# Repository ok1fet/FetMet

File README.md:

<!-- formatovani Markdown nebo html
kdyz neni obrazek 800x600 

<p>Celkové schéma zapojení.</p>
</p> 
-->

# FetMet APRS amatérská LoRa meteostanice

🟥**Nová verze poporuje posílání dat přes protokol MQTT**🟥

Meteostanice je postavena na vývojové desce ESP32 LILYGO T3 v1.6.1, která obsahuje integrovaný LoRa modul (433 MHz) a OLED displej. Díky tomu je celá konstrukce sondy výrazně zjednodušená.

Pro měření směru a rychlosti větru, srážek, atmosférického tlaku, teploty a vlhkosti stačí pouze tři elektronické součástky:
2× kondenzátor, 1× odpor a senzorový modul BME280.

Rychlost větru je měřena každých 20 sekund během intervalu 5 sekund.
Směr větru se vypočítává pomocí Yamartinova algoritmu, který vektorově zpracuje data a provádí korekci směrové odchylky.

Po 24 dvacetisekundových cyklech (tedy každých 10 minut) se provede měření tlaku, teploty a vlhkosti. Výsledná data jsou odesílána prostřednictvím sítě LoRa APRS.

Historická data lze sledovat online na:[www.aprs.fi](https://www.aprs.fi).

🌧️ Měření srážek
Srážky se detekují nepřetržitě s přesností 0,3 mm na impuls data se ukládají průběžně. Každých 10 minut (6 cyklus) se provede součet **6 a 144 polohového kruhového bufferu**, čímž získáme přehled za poslední hodinua den.

🔩 Použité senzory
Senzory pro vítr a srážky jsou převzaty z běžně dostupných meteostanic WH1080 / WH1090, které lze snadno zakoupit jako náhradní díly za přijatelnou cenu.

🧠 Software
Celý kód je bohatě okomentovaný a všechny výpočty jsou průběžně zobrazovány na sériové konzoli během běhu softwaru.

**Celkové schéma zapojení.**

Pohled na prototyp meteosondy MetFet 🙂.

**Doporučení pro solární provoz:**  
Vypni OLED úplně (jumper na GPIO4 propojen na GND)

Montáž sondy do vodotěsné krabičky.

Pohled na stranu plošného spoje.

## Spotřeba – naměřená na stole

| Režim                     | OLED zapnutý | OLED vypnutý (GPIO4 = LOW) |
|---------------------------|--------------|----------------------------|
| Deep-sleep                | 5,0 mA       | **1,9 mA**                 |
| Měření větru (3 s)        | 22 mA        | **19,5 mA**                |
| LoRa vysílání             | 89 mA        | **80 mA**                  |

Ukázka montáže za využití 3D tištěných dílů.

Detail konzole se senzory větru.

Testování J antény.

Upravené Moxon antény.

Orientační kalibrace srážkoměru za pomocí zahradního kolečka. 😅

## Co a jak přesně měří

| Velicina            | Rozlišení / přesnost               | Interval měření |
|---------------------|------------------------------------|-----------------|
| Rychlost větru      | 0,1 m/s (1 impuls ≈ 2,4 km/h)      | každých 20 s    |
| Směr větru          | 8 směrů + Yamartinův algoritmus    | každých 20 s    |
| Srážky              | 0,3 mm na impuls                   | nepřetržitě     |
| Teplota / vlhkost   | BME280                             | každých 5 min   |
| Atmosférický tlak   | BME280 (přepočet na hladinu moře)  | každých 5 min   |
| Napětí baterie      | 0,01 V                             | každých 5 min   |

Každých 5 minut se odesílá **plná APRS zpráva** (včetně `r000` a `p000`) → okamžitě vidět na  
https://aprs.fi/#!call=a%2FOK1FET-73

!!!U desky LILYGO není vyveden Vin pin. Zde je Vin bod pro připojení solárního panelu!!!
Nebo můžete solarní panel připojit přes mikro USB.

Průběh impulsu srážkoměru při změně za kondenzátor M1. Při 10pF občas detekovalo falešnou srážku!

Provozní zkoušky porovnávání nové sondy v přírodních podmínkách 💪😁

## Použité hlavvní komponenty
| Součástka                     | Kde koupit                                    | Cena cca |
|-------------------------------|-----------------------------------------------|----------|
| LILYGO T3 V1.6.1              | Laskakit, Aliexpress                          | 850 Kč   |
| BME280                        | Laskakit, GME                                 | 120 Kč   |
| Anemometr + směrovka WH1080   | Hadex, Aliexpress („WH1080 wind sensor“)      | 350 Kč   |
| Srážkoměr WH1080              | Hadex, Aliexpress („WH1080 rain gauge“)       | 350 Kč   |
| Solární panel 10×10 cm        | Aliexpress                                    | 150 Kč   |
| Li-Ion 18650                  | kdekoliv                                      | 100 Kč   |

**Celkem: 1600–1800 Kč**

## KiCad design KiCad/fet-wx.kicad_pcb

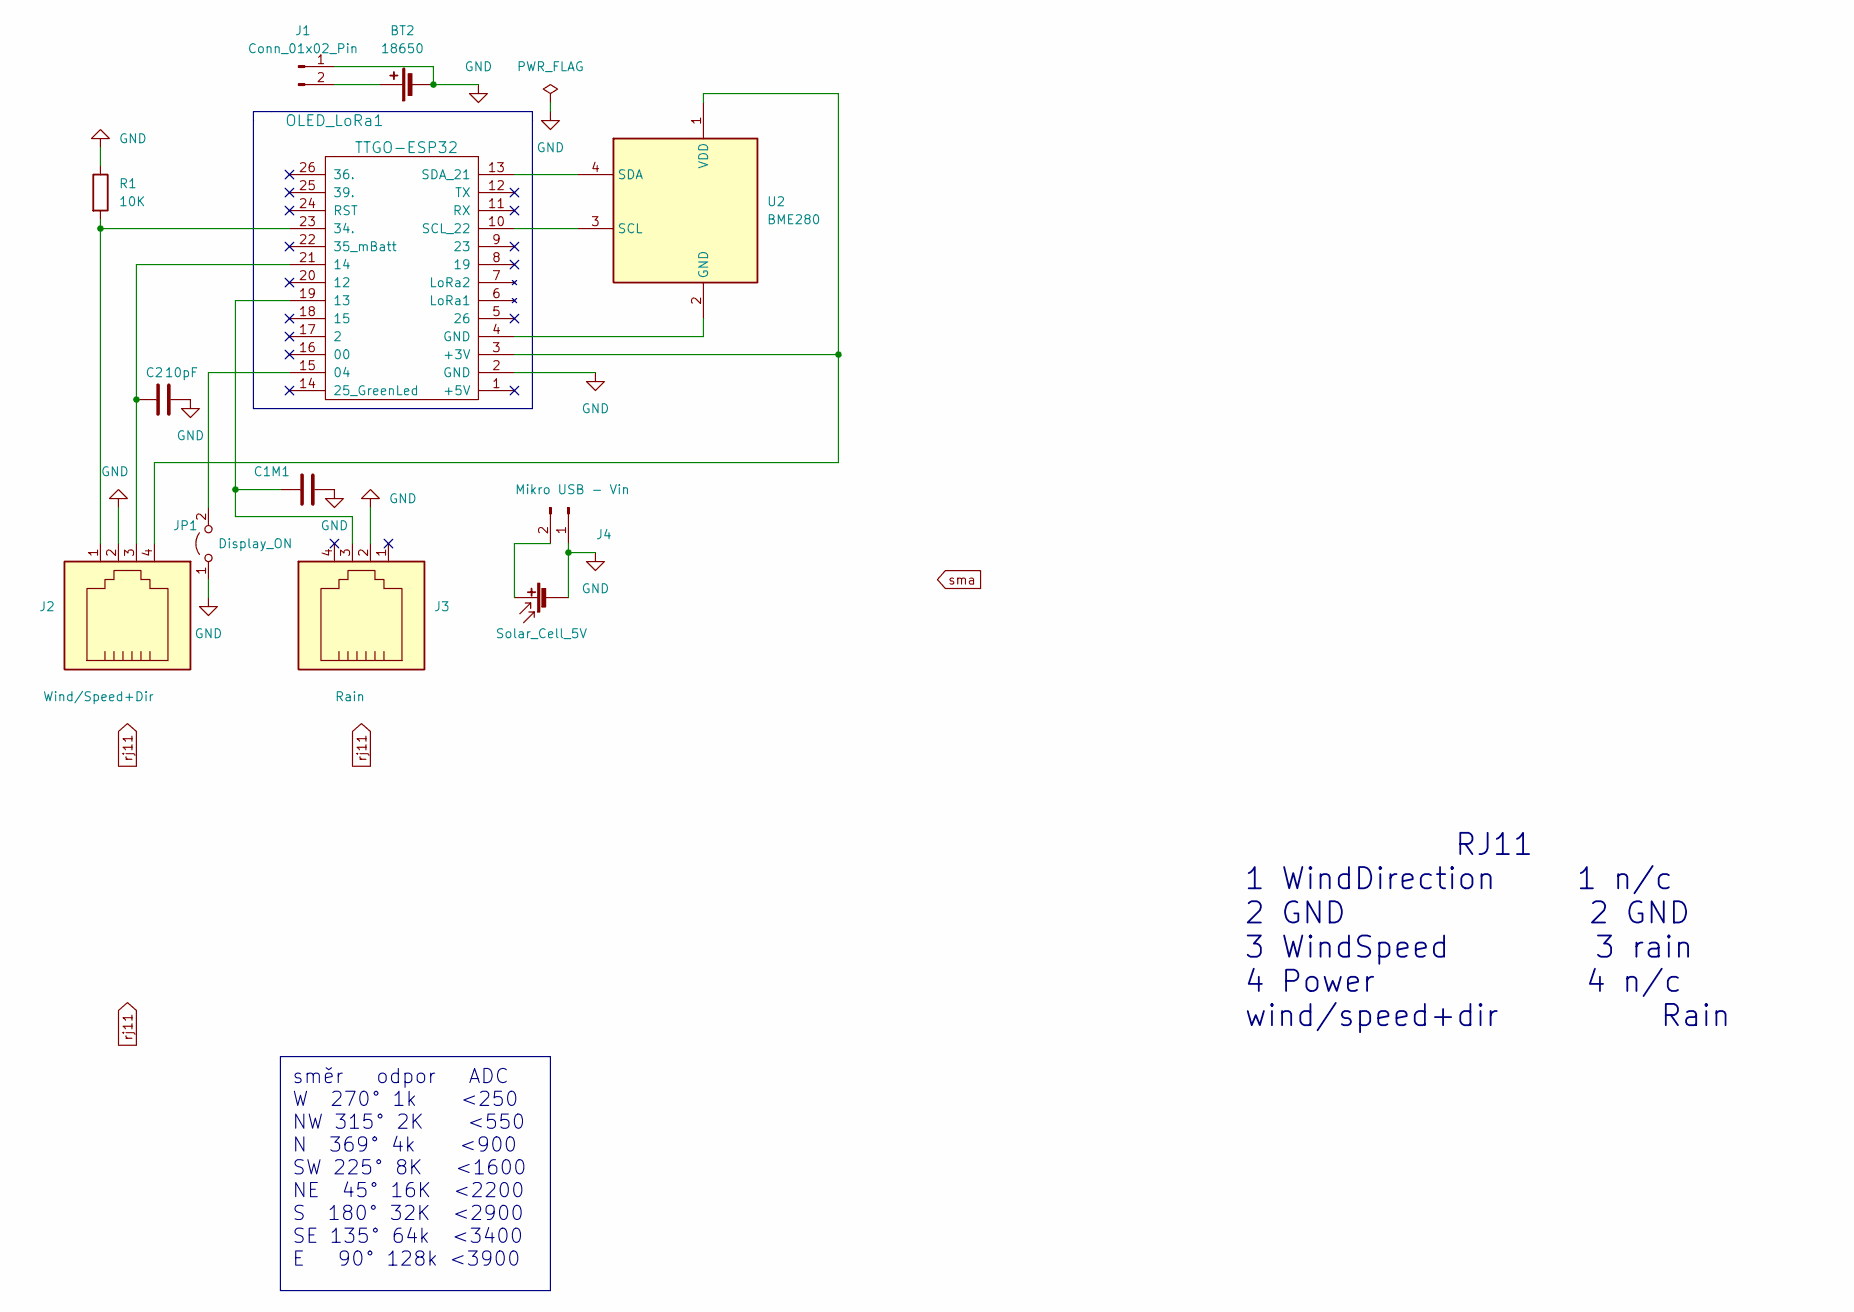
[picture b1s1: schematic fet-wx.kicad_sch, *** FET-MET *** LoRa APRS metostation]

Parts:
BT2: 18650; BatteryHolder_MPD_BH-18650-PC2
C1: M1; C_Disc_D5.0mm_W2.5mm_P2.50mm
C2: 10pF; C_Disc_D5.0mm_W2.5mm_P2.50mm
J1: Conn_01x02_Pin; PinHeader_1x02_P2.54mm_Vertical
J2: Wind/Speed+Dir; RJ14_Connfly_DS1133-S4_Horizontal
J3: Rain; RJ14_Connfly_DS1133-S4_Horizontal
J4: Mikro USB - Vin; PinHeader_1x02_P2.54mm_Vertical
JP1: Display_ON; PinHeader_1x02_P2.54mm_Vertical
OLED_LoRa1: TTGO-ESP32
R1: 10K; R_Axial_DIN0207_L6.3mm_D2.5mm_P7.62mm_Horizontal
SC1: Solar_Cell_5V; PinHeader_1x02_P2.54mm_Vertical
U2: BME280; PinHeader_1x04_P2.54mm_Vertical

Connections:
GND: BT2.2 (-), C1.2, C2.2, J1.1, J2.2, J3.2, J4.1, JP1.1 (A), OLED_LoRa1.2 (GND), R1.1, SC1.2 (-)
unnamed: BT2.1 (+), J1.2
unnamed: J4.2, SC1.1 (+)
unnamed: JP1.2 (B), OLED_LoRa1.15 (04)
unnamed: C1.1, J3.3, OLED_LoRa1.19 (13)
unnamed: C2.1, J2.3, OLED_LoRa1.21 (14)
unnamed: J2.1, OLED_LoRa1.23 (34.), R1.2
unnamed: J2.4, OLED_LoRa1.3 (+3V), U2.1 (VDD)
unnamed: OLED_LoRa1.10 (SCL_22), U2.3 (SCL)
unnamed: OLED_LoRa1.13 (SDA_21), U2.4 (SDA)
unnamed: OLED_LoRa1.4 (GND), U2.2 (GND)

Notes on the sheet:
směr odpor ADC W 270° 1k <250 NW 315° 2K <550 N 369° 4k <900 SW 225° 8K <1600 NE 45° 16K <2200 S 180° 32K <2900 SE 135° 64k <3400 E 90° 128k <3900
RJ11 1 WindDirection 1 n/c 2 GND 2 GND 3 WindSpeed 3 rain 4 Power 4 n/c wind/speed+dir Rain

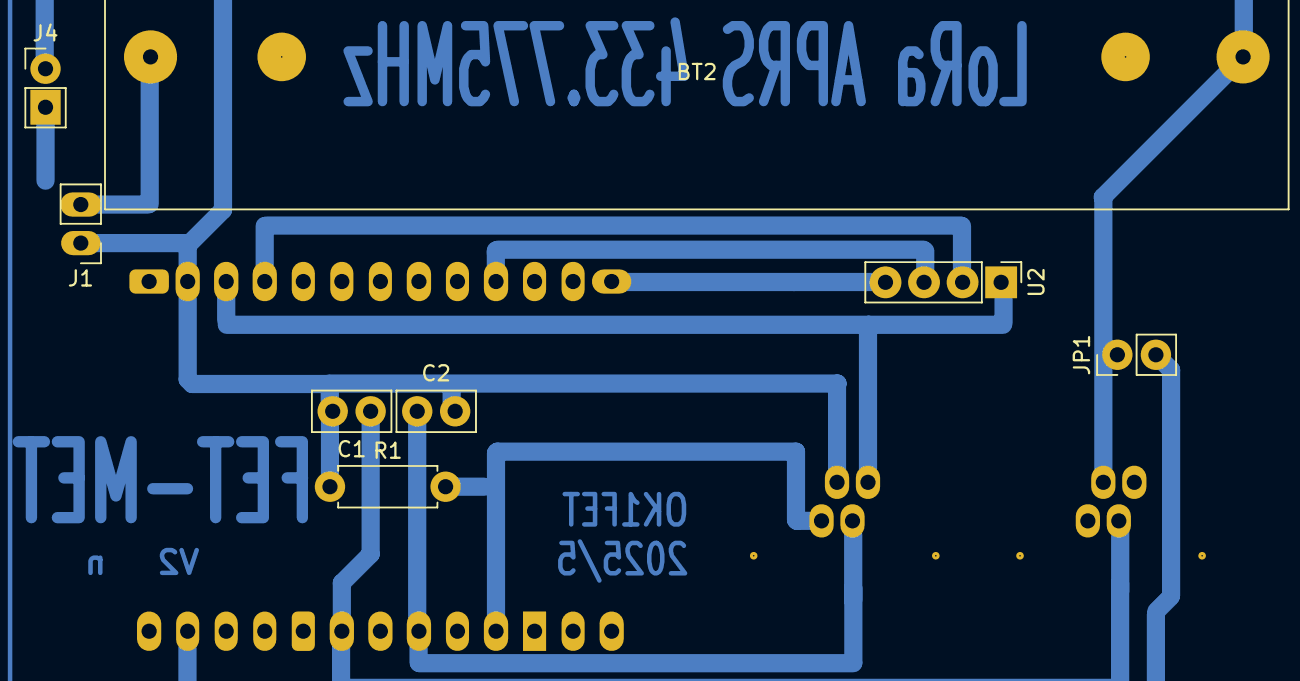
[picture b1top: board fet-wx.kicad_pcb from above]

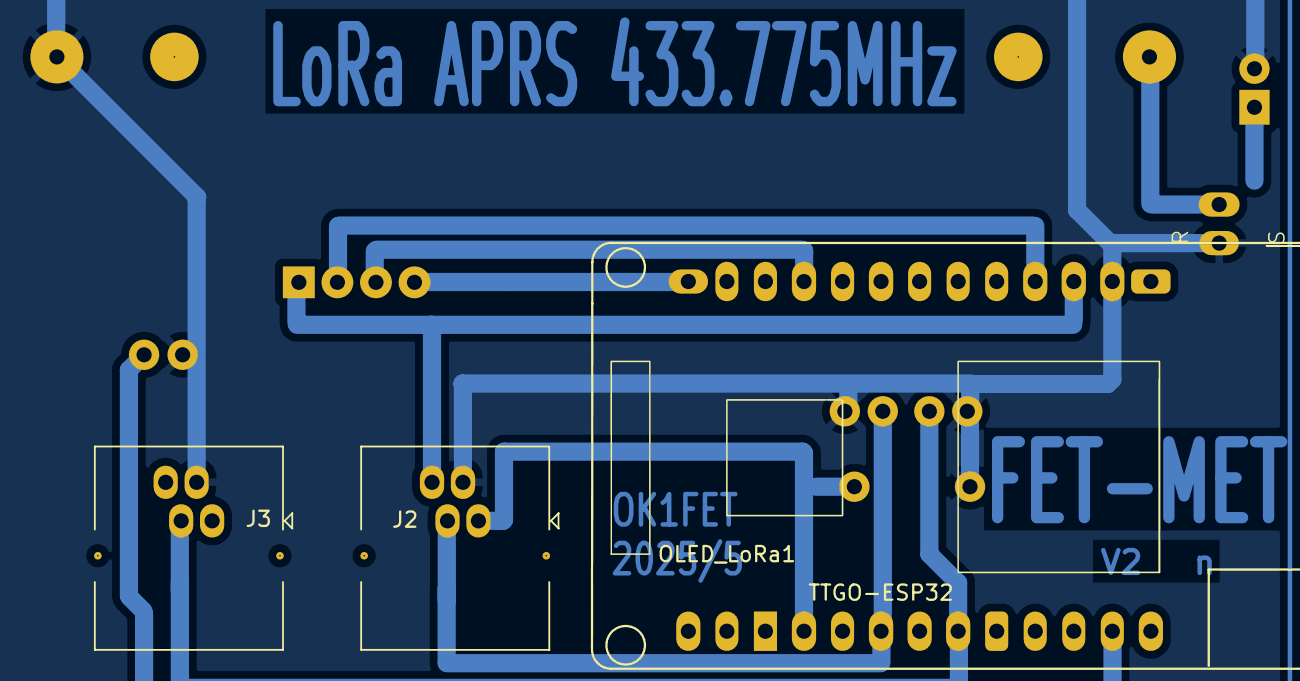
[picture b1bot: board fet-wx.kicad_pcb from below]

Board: 2 copper layers, 11 parts (3 on the bottom side), 10 nets.

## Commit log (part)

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2025-06-19 Create test
2025-06-19 Create Obrazky
2025-06-19 Create KiCad
2025-06-19 Create redmee
2025-06-19 Create redmme
2025-06-19 Update redmme
2025-06-20 Update redmee
2025-07-14 Create fetmet1d
2025-10-18 Add initial firmware for weather station with LoRa
    Initial commit of the weather station firmware with LoRa communication and various sensor integrations.
2025-10-19 Update meteostation and cycle counts
2025-10-23 Add LoRa weather station firmware
    Initial commit of the LoRa weather station code, including sensor readings, data processing, and communication setup.
2025-10-27 Add LoRa weather station firmware
    Combined DeepSleep 1 second and 20 seconds to reduce consumption.
2025-10-29 Refactor rain measurement logic and comments
    Updated calibration value for AD converter and adjusted buffer sizes for rain data. Improved comments and removed unused test code.
2025-11-05 Introduce rainCallCount for hourly data management
    Added rainCallCount to track hourly rain data storage.
2025-11-14 Add initial firmware for weather station with LoRa
    Initial commit of the weather station firmware for LoRa communication, including sensor integration and OLED display functionality.
2025-11-22 Adjust VREF calibration and enhance comments
    Updated calibration value for AD converter and improved comments for clarity.
2025-11-22 Update README with solar operation tips and components
    Added solar operation recommendations and component details.
2025-11-22 Revise rain measurement and power consumption details
    Updated details on rain measurement data storage and power consumption recommendations.
2025-11-22 Update rainfall measurement description in README
    Revised the section on rainfall measurements for clarity and conciseness.
2025-11-24 Refactor rain measurement and clean up code
    Removed test block and updated rain measurement logic.
